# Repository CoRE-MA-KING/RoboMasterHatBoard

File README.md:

# RoboMasterHatBoard
ロボマス開発ボード用ハットです。  
CoREに出場するロボットに利用しているメインボードとして[RoboMaster 開発ボードタイプA](https://store.dji.com/jp/product/rm-development-board-type-a?vid=42041)を利用しているので、このボードから2024年大会用に必要なピンをコネクタにまとめるための基板です。

# 機能
ロボマス開発ボードにはピンヘッダからいくつかのピンが出ているので、そこから今回のロボットで利用するピンを取り出します。

具体的に以下のピンを取り出します。
|ピン名|ペリフェラル|用途|備考|
|---|---|---|---|  
|PD12|TIM4_CH1| モータ1PWM用||
|PD13|TIM4_CH2| モータ2PWM用||
|PA0|TIM2_CH1| エンコーダ1 A相||
|PA1|TIM2_CH2| エンコーダ1 B相||
|PA2|GPIO_INPUT| エンコーダ1 Z相||
|PI5|TIM8_CH1| エンコーダ2 A相||
|PI6|TIM8_CH2| エンコーダ2 B相||
|PI7|GPIO_INPUT| エンコーダ2 Z相||
|PF0|GPIO_INPUT|フォトインタラプタ1入力|マイコンの内部プルアップ必須|
|PF1|GPIO_INPUT|フォトインタラプタ2入力|マイコンの内部プルアップ必須|
|PE6|GPIO_INPUT|非常停止ボタン入力|マイコンの内部プルアップ必須|
|PE12|GPIO_OUTPUT|リレー駆動信号||
|PC3|GPIO_INPUT|撃破信号入力|PC3は5 Vトレラントなので5 V入力可能|
|PC1|GPIO|汎用GPIO|予備ポート 5 Vトレラントピン|

v0.1の基板上のシルクと回路図上の信号線が逆になっているので注意。回路図が間違っているということにして基板のシルクか上の表に従えばOK。

基板上のコネクタのピンアサインは次の通り
### MOTOR PWM
|1|2|3|
|---|---|---|
|TIM4_CH1(PD12)|TIM4_CH2(PD13)|GND|

### PHOTO SENS1
|1|2|3|
|---|---|---|
|5 V|INPUT(PF0)|GND|

### PHOTO SENS2
|1|2|3|
|---|---|---|
|5 V|INPUT(PF1)|GND|

### ENC1
|1|2|3|4|5|
|---|---|---|---|---|
|3.3 V|TIM2_CH1(PA1)|TIM2_CH2(PA2)|INPUT(PA2)|GND|

### ENC2
|1|2|3|4|5|
|---|---|---|---|---|
|3.3 V|TIM8_CH1(PI5)|TIM8_CH2(Pi6)|INPUT(PI7)|GND|

### RELAY
|1|2|
|---|---|
|OUTPUT(PE12)|GND|

### ESW
|1|2|
|---|---|
|INPUT(PE6)|GND|

### BREAK
|1|2|
|---|---|
|INPUT(PC3)|GND|

### 予備ポート
|1|2|
|---|---|
|INPUT(PC1)|GND|

## 参考
ロボマス開発ボードピンヘッダ部分のピンアサインは[回路図](https://ausdroid.co/wp-content/uploads/2020/08/RoboMaster-Development-Board-Type-A-Schematic.pdf)より

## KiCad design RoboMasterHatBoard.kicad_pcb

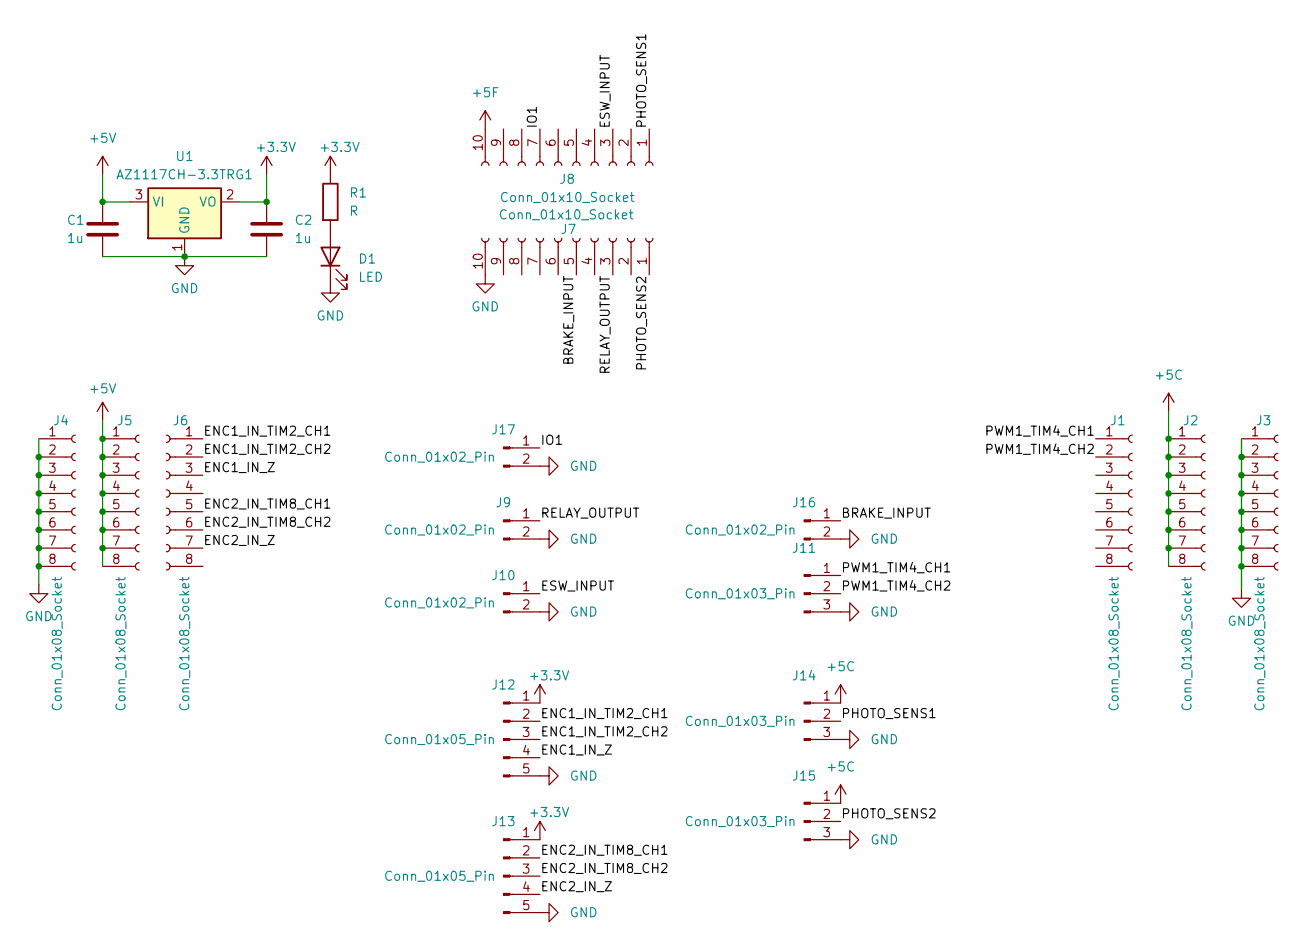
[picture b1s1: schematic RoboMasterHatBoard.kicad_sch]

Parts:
C1, C2: 1u; C_0402_1005Metric
D1: LED; D_0603_1608Metric
J1, J2, J3, J4, J5, J6: Conn_01x08_Socket; PinHeader_1x08_P2.54mm_Vertical
J7, J8: Conn_01x10_Socket; PinHeader_1x10_P2.54mm_Vertical
J9, J10, J16, J17: Conn_01x02_Pin; JST_XH_B2B-XH-A_1x02_P2.50mm_Vertical
J11, J14, J15: Conn_01x03_Pin; JST_XH_B3B-XH-A_1x03_P2.50mm_Vertical
J12, J13: Conn_01x05_Pin; JST_XH_B5B-XH-A_1x05_P2.50mm_Vertical
R1: R; R_0402_1005Metric
U1: AZ1117CH-3.3TRG1; SOT-223-3_TabPin2

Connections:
+3.3V: C2.1, J12.1, J13.1, R1.1, U1.2 (VO)
+5C: J2.1, J2.2, J2.3, J2.4, J2.5, J2.6, J2.7, J2.8, J14.1, J15.1
+5F: J8.10
+5V: C1.1, J5.1, J5.2, J5.3, J5.4, J5.5, J5.6, J5.7, J5.8, U1.3 (VI)
/BRAKE_INPUT: J7.5, J16.1
/ENC1_IN_TIM2_CH1: J6.1, J12.2
/ENC1_IN_TIM2_CH2: J6.2, J12.3
/ENC1_IN_Z: J6.3, J12.4
/ENC2_IN_TIM8_CH1: J6.5, J13.2
/ENC2_IN_TIM8_CH2: J6.6, J13.3
/ENC2_IN_Z: J6.7, J13.4
/ESW_INPUT: J8.3, J10.1
/IO1: J8.7, J17.1
/PHOTO_SENS1: J8.1, J14.2
/PHOTO_SENS2: J7.1, J15.2
/PWM1_TIM4_CH1: J1.1, J11.1
/PWM1_TIM4_CH2: J1.2, J11.2
/RELAY_OUTPUT: J7.3, J9.1
GND: C1.2, C2.2, D1.1 (K), J3.1, J3.2, J3.3, J3.4, J3.5, J3.6, J3.7, J3.8, J4.1, J4.2, J4.3, J4.4, J4.5, J4.6, J4.7, J4.8, J7.10, J9.2, J10.2, J11.3, J12.5, J13.5, J14.3, J15.3, J16.2, J17.2, U1.1 (GND)
unnamed: D1.2 (A), R1.2

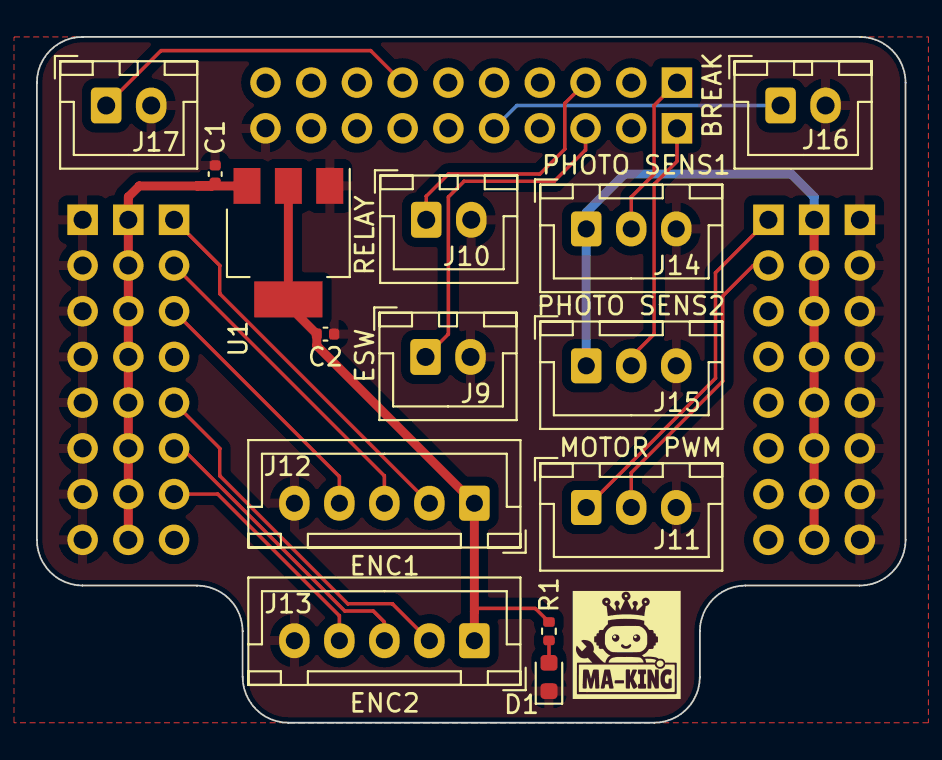
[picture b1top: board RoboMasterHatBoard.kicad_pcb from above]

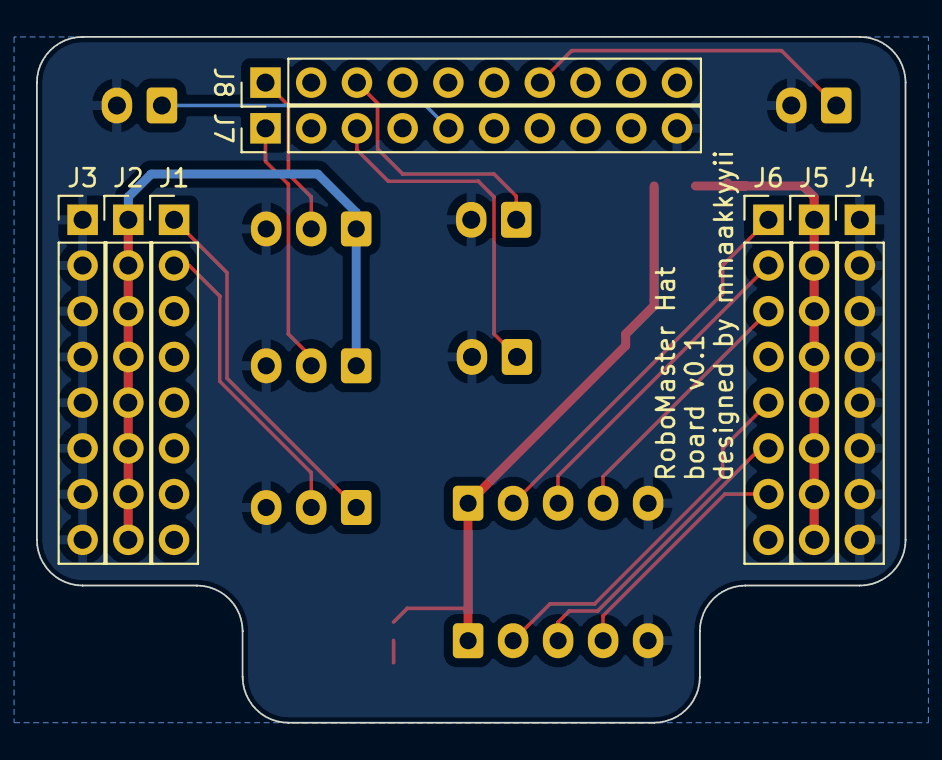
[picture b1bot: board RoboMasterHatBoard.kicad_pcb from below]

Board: 2 copper layers, 48.3 x 38.1 mm, 23 parts (8 on the bottom side), 19 nets.

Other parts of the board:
 : LOGO

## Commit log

2024-01-18 撃破入力ピンを追加
2024-01-20 add gerber
2024-02-21 readme追加
2024-02-21 ピンアサイン追記
2024-02-21 画像追加
